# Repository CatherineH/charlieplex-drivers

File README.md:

# charlieplex-drivers
The same driver for an adafruit 9x16 charlieplexed matrix implemented in several languages and pieces of hardware.

## Compiling the Verilog Version for the DE0-Nano

Download and install [python-quartus](https://github.com/CatherineH/python-quartus). Then, run the command:

```
pyquartus -u -p verilog_version
```

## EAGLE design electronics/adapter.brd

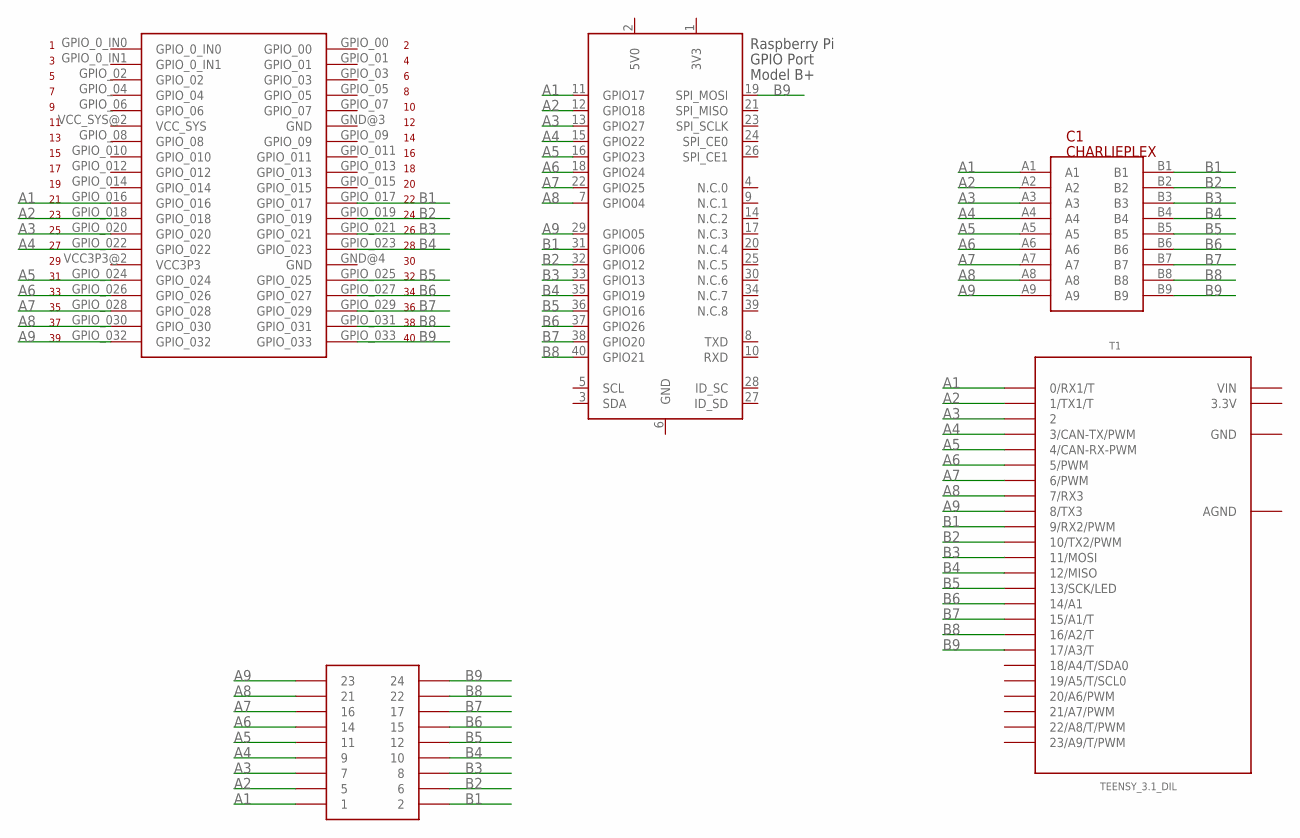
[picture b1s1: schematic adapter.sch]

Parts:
C1: CHARLIEPLEX; CHARLIEPLEXED
T1: TEENSY_3.1_DIL; TEENSY3-DIL
U$1: MOJO_V2_HEADER1_CHOPPED
U$2: DE0_NANO_JP1
X1: RASPI_GPIO_B+_PIN

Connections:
3.3V: T1.3.3V
3V3: X1.1 (3V3)
5V0: X1.2 (5V0)
A1: C1.A1, T1.0 (0/RX1/T), U$1.1, U$2.GPIO_016, X1.11 (GPIO17)
A2: C1.A2, T1.1 (1/TX1/T), U$1.5, U$2.GPIO_018, X1.12 (GPIO18)
A3: C1.A3, T1.2, U$1.7, U$2.GPIO_020, X1.13 (GPIO27)
A4: C1.A4, T1.3 (3/CAN-TX/PWM), U$1.9, U$2.GPIO_022, X1.15 (GPIO22)
A5: C1.A5, T1.4 (4/CAN-RX-PWM), U$1.11, U$2.GPIO_024, X1.16 (GPIO23)
A6: C1.A6, T1.5 (5/PWM), U$1.14, U$2.GPIO_026, X1.18 (GPIO24)
A7: C1.A7, T1.6 (6/PWM), U$1.16, U$2.GPIO_028, X1.22 (GPIO25)
A8: C1.A8, T1.7 (7/RX3), U$1.21, U$2.GPIO_030, X1.7 (GPIO04)
A9: C1.A9, T1.8 (8/TX3), U$1.23, U$2.GPIO_032, X1.29 (GPIO05)
AGND: T1.AGND
B1: C1.B1, T1.9 (9/RX2/PWM), U$1.2, U$2.GPIO_017, X1.31 (GPIO06)
B2: C1.B2, T1.10 (10/TX2/PWM), U$1.6, U$2.GPIO_019, X1.32 (GPIO12)
B3: C1.B3, T1.11 (11/MOSI), U$1.8, U$2.GPIO_021, X1.33 (GPIO13)
B4: C1.B4, T1.12 (12/MISO), U$1.10, U$2.GPIO_023, X1.35 (GPIO19)
B5: C1.B5, T1.13 (13/SCK/LED), U$1.12, U$2.GPIO_025, X1.36 (GPIO16)
B6: C1.B6, T1.14/A0 (14/A1), U$1.15, U$2.GPIO_027, X1.37 (GPIO26)
B7: C1.B7, T1.15/A1 (15/A1/T), U$1.17, U$2.GPIO_029, X1.38 (GPIO20)
B8: C1.B8, T1.16/A2 (16/A2/T), U$1.22, U$2.GPIO_031, X1.40 (GPIO21)
B9: C1.B9, T1.17/A3 (17/A3/T), U$1.24, U$2.GPIO_033, X1.19 (SPI_MOSI)
GND: T1.GND, U$2.GND@3 (GND), U$2.GND@4 (GND), X1.6 (GND)
VCC3P3: U$2.VCC3P3@2 (VCC3P3)
VCC_SYS: U$2.VCC_SYS@2 (VCC_SYS)
VIN: T1.VIN

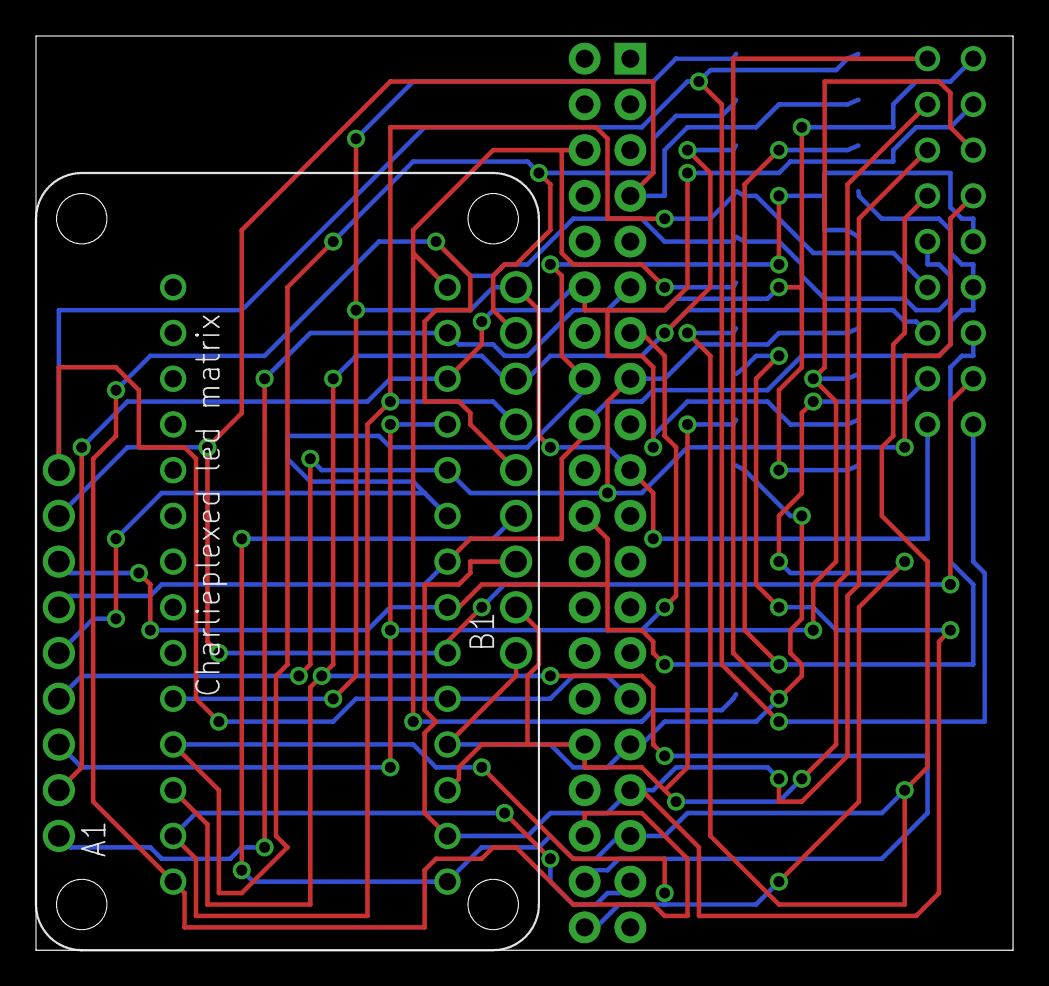
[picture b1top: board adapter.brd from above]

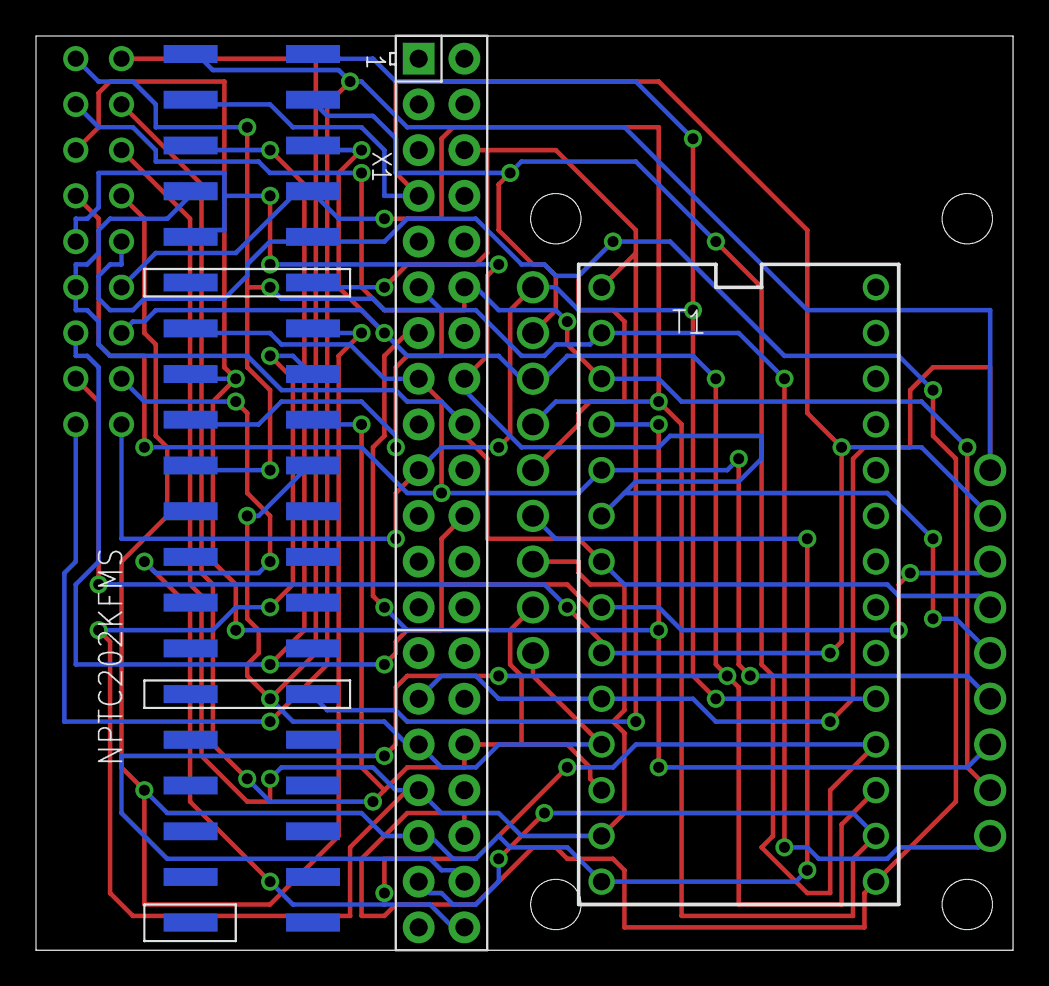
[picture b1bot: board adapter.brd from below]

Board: 2 copper layers, 54.3 x 50.8 mm, 5 parts (3 on the bottom side), 19 nets.

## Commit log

2016-06-23 added start of charlieplex animation
2016-06-23 adding animation generation script
2016-06-23 compiling to gif
2016-07-26 add generate animation
2016-08-13 starting embed svg
2016-08-13 added LED matrix animation
2016-08-18 created led matrix animation
2016-08-24 switching to snap.js
2016-09-02 changing to object oriented approach on schematic
2016-09-03 blocnote changes to generate charlieplex animation
2016-09-04 added svg cloning
2016-09-05 started making map
2016-09-06 switched to CDN
2016-09-07 state before chopping up the node connections by rules
2016-09-07 re-added all of the connections
2016-09-08 fixed connections
2016-09-08 added animation on traversing network
2016-12-03 moved all the core to a verilog directory
2016-12-03 added adapter schematic
